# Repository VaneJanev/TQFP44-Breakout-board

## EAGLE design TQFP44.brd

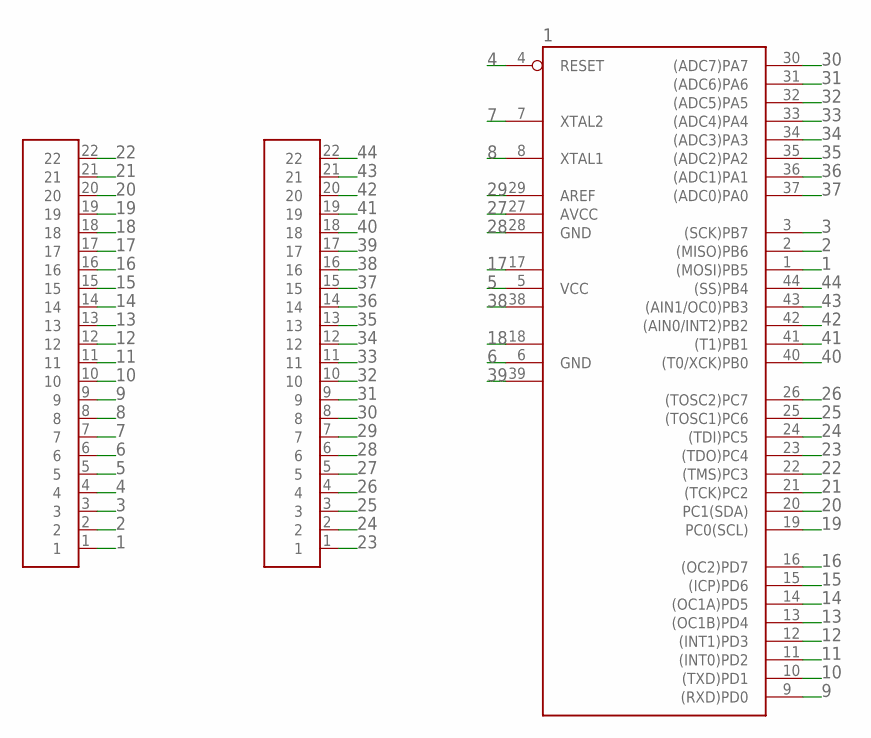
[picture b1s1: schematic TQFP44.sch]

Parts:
1: MEGA32-A; TQFP44
2: 1X22THM; 1X22
U$3: 1X22THM; 1X22

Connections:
1: 1.1 ((MOSI)PB5), 2.1
2: 1.2 ((MISO)PB6), 2.2
3: 1.3 ((SCK)PB7), 2.3
4: 1.4 (RESET), 2.4
5: 1.5 (VCC), 2.5
6: 1.6 (GND), 2.6
7: 1.7 (XTAL2), 2.7
8: 1.8 (XTAL1), 2.8
9: 1.9 ((RXD)PD0), 2.9
10: 1.10 ((TXD)PD1), 2.10
11: 1.11 ((INT0)PD2), 2.11
12: 1.12 ((INT1)PD3), 2.12
13: 1.13 ((OC1B)PD4), 2.13
14: 1.14 ((OC1A)PD5), 2.14
15: 1.15 ((ICP)PD6), 2.15
16: 1.16 ((OC2)PD7), 2.16
17: 1.17 (VCC1), 2.17
18: 1.18 (GND1), 2.18
19: 1.19 (PC0(SCL)), 2.19
20: 1.20 (PC1(SDA)), 2.20
21: 1.21 ((TCK)PC2), 2.21
22: 1.22 ((TMS)PC3), 2.22
23: 1.23 ((TDO)PC4), U$3.1
24: 1.24 ((TDI)PC5), U$3.2
25: 1.25 ((TOSC1)PC6), U$3.3
26: 1.26 ((TOSC2)PC7), U$3.4
27: 1.27 (AVCC), U$3.5
28: 1.28 (GND), U$3.6
29: 1.29 (AREF), U$3.7
30: 1.30 ((ADC7)PA7), U$3.8
31: 1.31 ((ADC6)PA6), U$3.9
32: 1.32 ((ADC5)PA5), U$3.10
33: 1.33 ((ADC4)PA4), U$3.11
34: 1.34 ((ADC3)PA3), U$3.12
35: 1.35 ((ADC2)PA2), U$3.13
36: 1.36 ((ADC1)PA1), U$3.14
37: 1.37 ((ADC0)PA0), U$3.15
38: 1.38 (VCC2), U$3.16
39: 1.39 (GND2), U$3.17
40: 1.40 ((T0/XCK)PB0), U$3.18
41: 1.41 ((T1)PB1), U$3.19
42: 1.42 ((AIN0/INT2)PB2), U$3.20
43: 1.43 ((AIN1/OC0)PB3), U$3.21
44: 1.44 ((SS)PB4), U$3.22

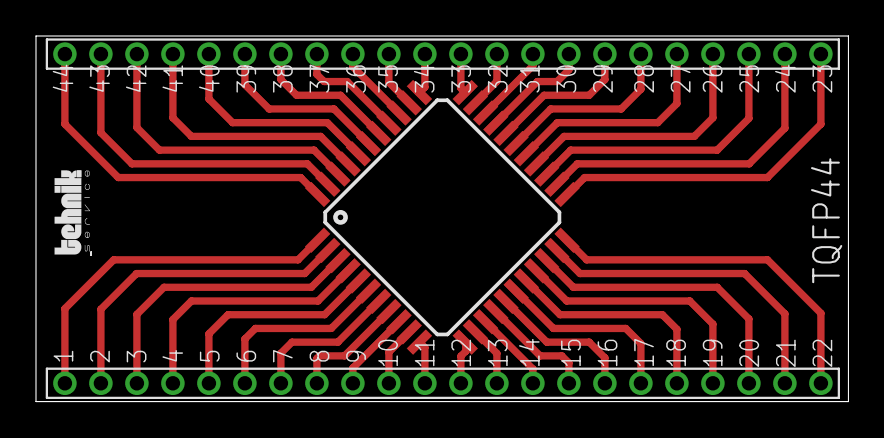
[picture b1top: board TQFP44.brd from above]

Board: 2 copper layers, 45.1 x 20.3 mm, 4 parts (0 on the bottom side), 44 nets.

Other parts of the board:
U$1: LOGOT

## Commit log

2015-06-03 :neckbeard: Added .gitattributes
2015-06-03 TQFP44 Breakout board
    Eagle Design Files
